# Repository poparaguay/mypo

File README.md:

# MyPO Board

Myo Armband + PO Paraguay
========
A board that connects the different parts of the system, demonimated MyPo. It is the interface between the Myo Armband sensor and the advanced prosthetic. It is composed of an Arduino board and a Bluetooth 4.0 module, with a custom firmware. Next are the different parts that compose this board.

Components
----

* MyPo Board
    ```
    
    Designed by Po Paraguay and manufactured by https://oshpark.com/ by uploading the mypo.brd file to the webpage
    
    Allows to flash the bluetooth module from the board itself
    
    ```
* Bluetooth BLE HM-11 CC2541 SoC 
    ```
    
    Flash the board by following these steps: https://github.com/RedBearLab/CCLoader
    
    Flash this file  "MyoBridge_CC2541.hex" to the CC2541 chip
     
    ```
* Arduino Pro Mini 328 5V/16Mhz.
* MicroServo 

    ```
    
    3 x TowerPro MG92B.  (Torque (4.8v): 3.1kg/cm - (6.0v): 3.5kg/cm)
    
    ```
    
* Battery: Li-Ion 1S 2500mAh 18650 
* Charge/Discharge module with voltage protection:

    ```
    http://goo.gl/Kd2iIu 
    
    ```
* 3.3V Regulator
    ```
AMS11171A LOW DROPOUT VOLTAGE REGULATOR 
http://www.advanced-monolithic.com/pdf/ds1117.pdf
    ```

*Passive components SMD  (0805: 0.08" × 0.05" (2,0 mm × 1,25 mm)  1/8 W)
    ```
- Resistors 1R/2R, where 1R is the value of any resistor and 2R is the double of that
-  100nF Capacitor
    ```

Characteristics
----

* Does not need an external computer to run
* The actual processing of the data is done by the Myo armband
* Uses the MyoBridge library:
    ```
    https://github.com/vroland/MyoBridge 
    ```
* Independent control of up to 3 servos: 
    ```
    SERVO1 : Port 5
    
    SERVO2 : Port 6
    
    GPIO1  : Port 9
    
    ```
* Virtual communication (Bluetooth - Arduino)
    ```
    
    RX Arduino to TX Bluetooth : Port 2
    
    TX Arduino to RX Bluetooth : Port 3
   
    ```

Author
----------
* Mateo Acosta - macosta@po.com.py

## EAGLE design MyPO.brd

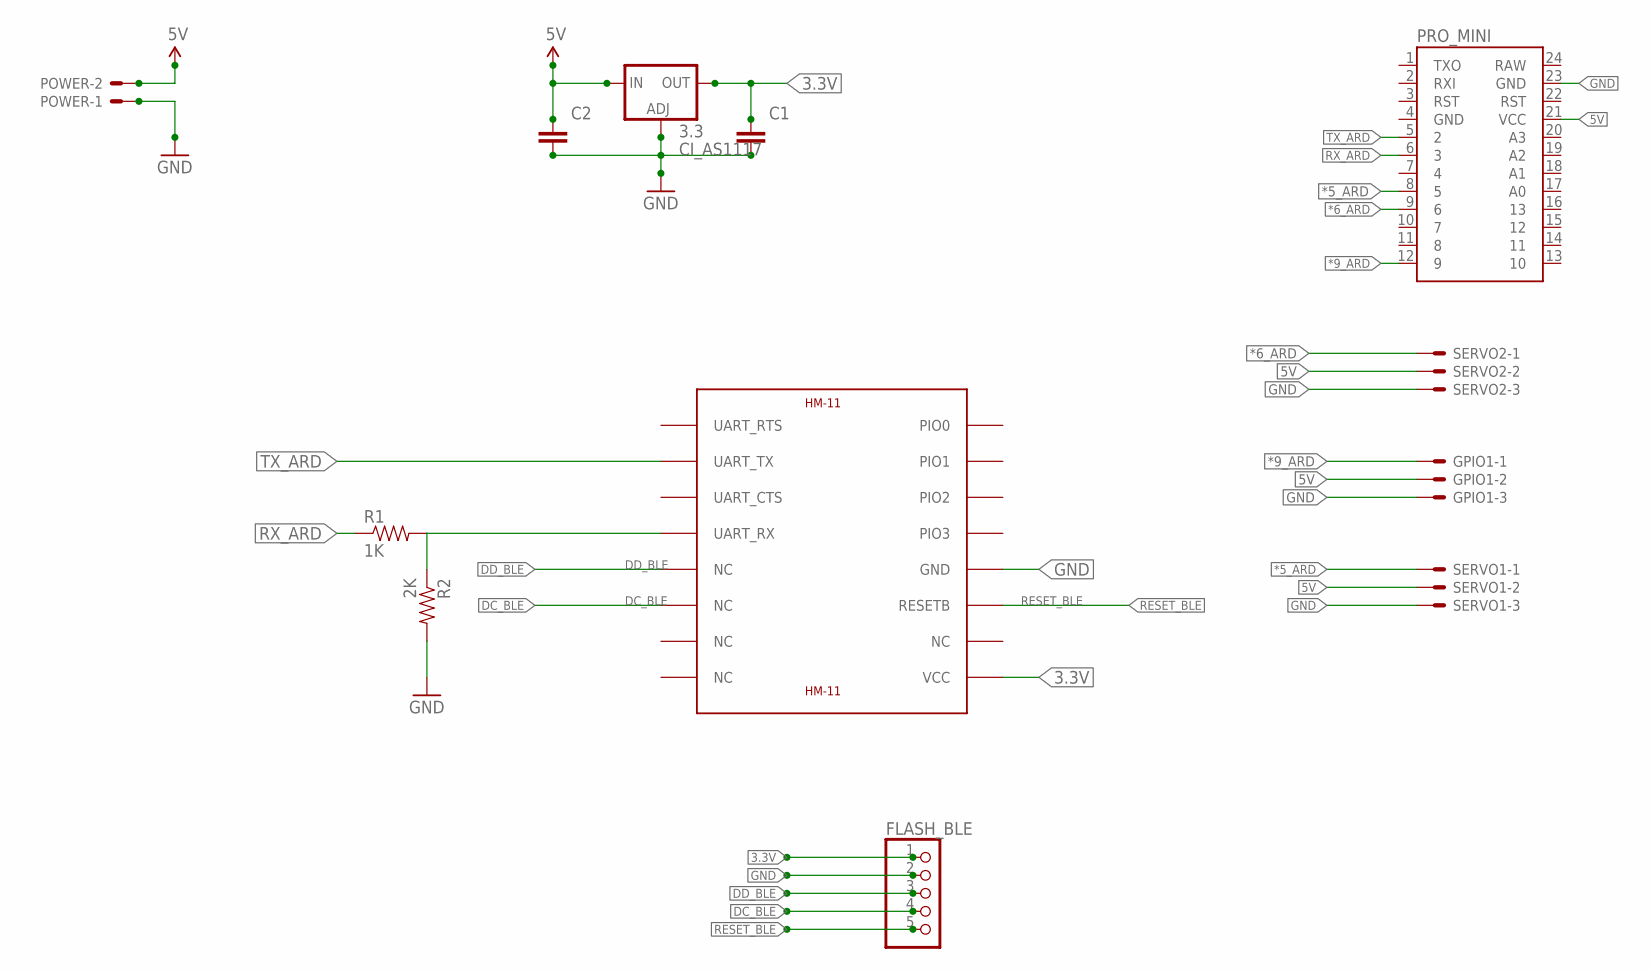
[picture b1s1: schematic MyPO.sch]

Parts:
3.3: CI_AS1117; DPACK
BLE: HM-11
C1, C2: CAPACITOR-0805; C0805
FLASH_BLE: PINHD-1X55X2MM; 1_05X2MM
GPIO1: JST-XH-03-PIN-LONG-PAD; JST-XH-03-PACKAGE-LONG-PAD
POWER: JST-XH-02-PIN-LONG-PAD; JST-XH-02-PACKAGE-LONG-PAD
PRO_MINI: ARDUINO_MINI
R1: 1K; R0805
R2: 2K; R0805
SERVO1, SERVO2: JST-XH-03-PIN-LONG-PAD; JST-XH-03-PACKAGE-LONG-PAD

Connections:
3.3V: 3.3.4 (OUT), BLE.VCC, C1.1, FLASH_BLE.1
5V: 3.3.3 (IN), C2.1, GPIO1.2, POWER.2, PRO_MINI.21 (VCC), SERVO1.2, SERVO2.2
*5_ARD: PRO_MINI.8 (5), SERVO1.1
*6_ARD: PRO_MINI.9 (6), SERVO2.1
*9_ARD: GPIO1.1, PRO_MINI.12 (9)
DC_BLE: BLE.NC@6 (NC), FLASH_BLE.4
DD_BLE: BLE.NC@5 (NC), FLASH_BLE.3
GND: 3.3.1 (ADJ), BLE.GND, C1.2, C2.2, FLASH_BLE.2, GPIO1.3, POWER.1, PRO_MINI.23 (GND), R2.2, SERVO1.3, SERVO2.3
unnamed: BLE.UART_RX, R1.2, R2.1
RESET_BLE: BLE.RESETB, FLASH_BLE.5
RX_ARD: PRO_MINI.6 (3), R1.1
TX_ARD: BLE.UART_TX, PRO_MINI.5 (2)

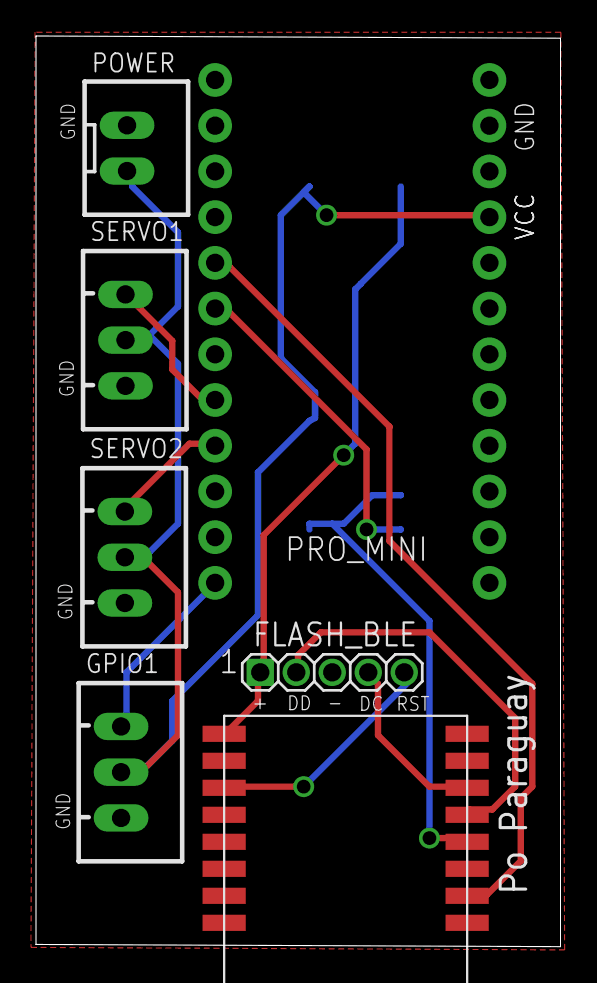
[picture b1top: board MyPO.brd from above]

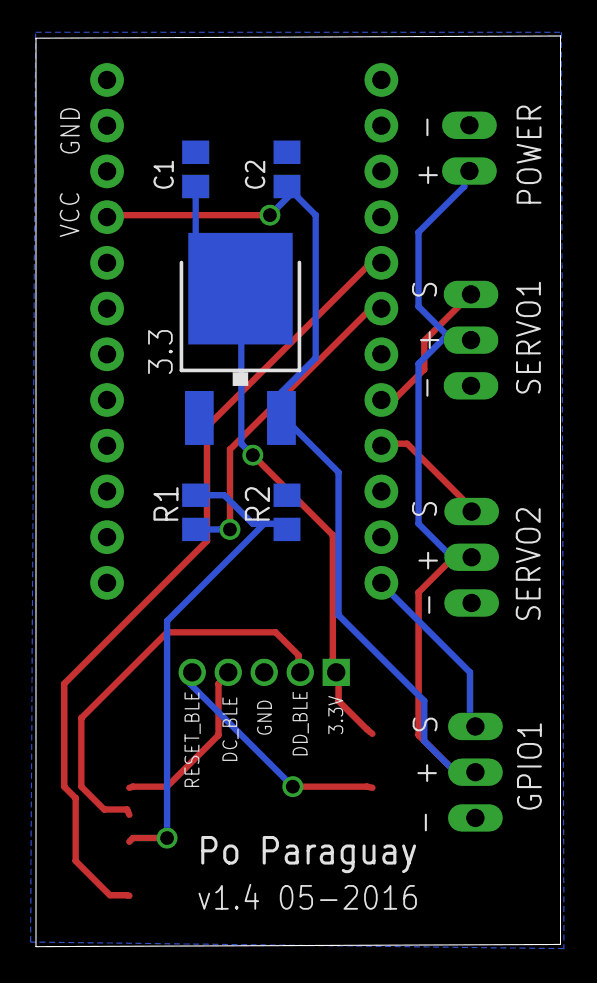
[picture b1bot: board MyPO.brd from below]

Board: 2 copper layers, 29.1 x 50.6 mm, 12 parts (5 on the bottom side), 12 nets.

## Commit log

2016-07-29 Create board

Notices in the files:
parts and their libraries:
SparkFun-Boards: Licensing: Creative Commons ShareAlike 4.0 International - https://creativecommons.org/licenses/by-sa/4.0
